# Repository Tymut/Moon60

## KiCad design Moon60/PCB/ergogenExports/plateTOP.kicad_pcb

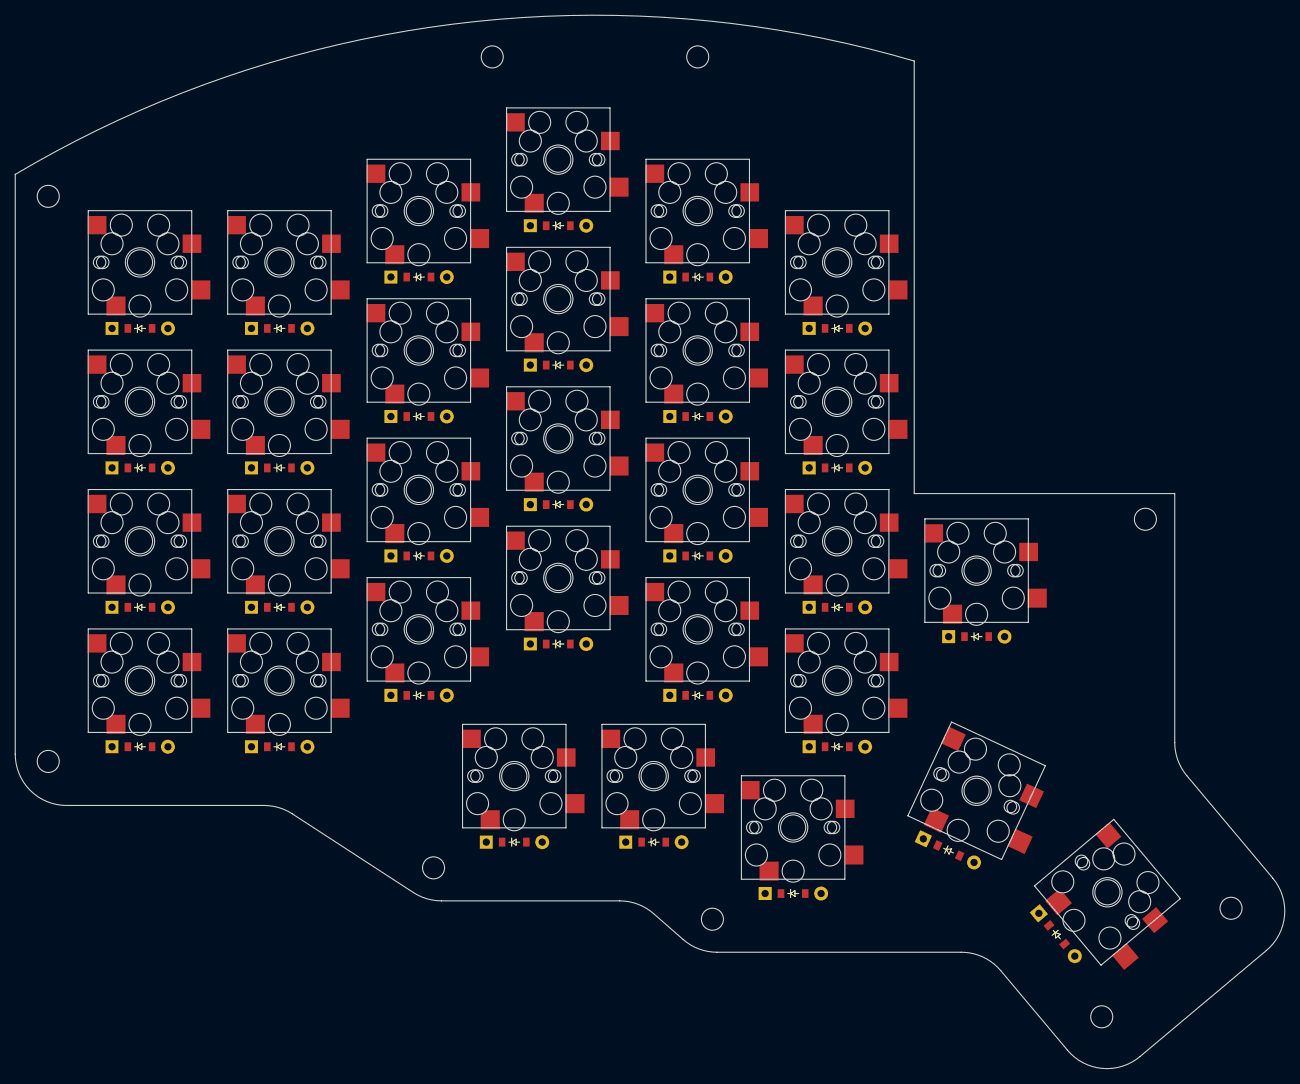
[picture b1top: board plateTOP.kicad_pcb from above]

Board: 2 copper layers, 173.0 x 143.5 mm, 90 parts (0 on the bottom side), 11 nets, no tracks yet.

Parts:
D1, D2, D3, D4, D5, D6, D7, D8, D9, D10, D11, D12, D13, D14, D15, D16, D17, D18, D19, D20, D21, D22, D23, D24, D25, D26, D27, D28, D29, D30: ComboDiode
S1, S3, S5, S7, S9, S11, S13, S15, S17, S19, S21, S23, S25, S27, S29, S31, S33, S35, S37, S39, S41, S43, S45, S47, S49, S51, S53, S55, S57, S59: PG1350
S2, S4, S6, S8, S10, S12, S14, S16, S18, S20, S22, S24, S26, S28, S30, S32, S34, S36, S38, S40, S42, S44, S46, S48, S50, S52, S54, S56, S58, S60: MX

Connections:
P4: D4.1, D4.2, D8.1, D8.2, D12.1, D12.2, D16.1, D16.2, D20.1, D20.2, D24.1, D24.2, S7.2, S8.1, S15.2, S16.1, S23.2, S24.1, S31.2, S32.1, S39.2, S40.1, S47.2, S48.1
P5: D3.1, D3.2, D7.1, D7.2, D11.1, D11.2, D15.1, D15.2, D19.1, D19.2, D23.1, D23.2, S5.2, S6.1, S13.2, S14.1, S21.2, S22.1, S29.2, S30.1, S37.2, S38.1, S45.2, S46.1
P6: D2.1, D2.2, D6.1, D6.2, D10.1, D10.2, D14.1, D14.2, D18.1, D18.2, D22.1, D22.2, S3.2, S4.1, S11.2, S12.1, S19.2, S20.1, S27.2, S28.1, S35.2, S36.1, S43.2, S44.1
P7: D1.1, D1.2, D5.1, D5.2, D9.1, D9.2, D13.1, D13.2, D17.1, D17.2, D21.1, D21.2, S1.2, S2.1, S9.2, S10.1, S17.2, S18.1, S25.2, S26.1, S33.2, S34.1, S41.2, S42.1
P8: D25.1, D25.2, D26.1, D26.2, D27.1, D27.2, D28.1, D28.2, D29.1, D29.2, D30.1, D30.2, S49.2, S50.1, S51.2, S52.1, S53.2, S54.1, S55.2, S56.1, S57.2, S58.1, S59.2, S60.1
P14: D21.1, D21.2, D22.1, D22.2, D23.1, D23.2, D24.1, D24.2, D30.1, D30.2, S41.1, S42.2, S43.1, S44.2, S45.1, S46.2, S47.1, S48.2, S59.1, S60.2
P15: D17.1, D17.2, D18.1, D18.2, D19.1, D19.2, D20.1, D20.2, D29.1, D29.2, S33.1, S34.2, S35.1, S36.2, S37.1, S38.2, S39.1, S40.2, S57.1, S58.2
P18: D13.1, D13.2, D14.1, D14.2, D15.1, D15.2, D16.1, D16.2, D28.1, D28.2, S25.1, S26.2, S27.1, S28.2, S29.1, S30.2, S31.1, S32.2, S55.1, S56.2
P19: D9.1, D9.2, D10.1, D10.2, D11.1, D11.2, D12.1, D12.2, D27.1, D27.2, S17.1, S18.2, S19.1, S20.2, S21.1, S22.2, S23.1, S24.2, S53.1, S54.2
P20: D5.1, D5.2, D6.1, D6.2, D7.1, D7.2, D8.1, D8.2, D26.1, D26.2, S9.1, S10.2, S11.1, S12.2, S13.1, S14.2, S15.1, S16.2, S51.1, S52.2
P21: D1.1, D1.2, D2.1, D2.2, D3.1, D3.2, D4.1, D4.2, D25.1, D25.2, S1.1, S2.2, S3.1, S4.2, S5.1, S6.2, S7.1, S8.2, S49.1, S50.2
